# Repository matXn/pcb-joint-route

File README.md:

# PCB 多网络联合布线挑战

给定已经摆好元件的 PCB，让布线算法为多条网络一起决定走向、层和过孔。最想解决的问题是：**一条线准备占用狭窄通道时，算法能否预见其他网络要为它多绕多远，并在落线前改选方案？**

在 ESP32-S3-MINI-1 的一次实验中，GPIO46 从 3 个过孔减到了 1 个，和它争用空间的 GPIO38 却从 5.81 mm 绕到了 20.65 mm。只看 GPIO46 会把这次修改判为成功。这个题要求连同 GPIO38 和其余网络，一起衡量整组方案的代价。

## 要做什么

输入是板框、焊盘、网表、允许的层、设计规则和已经固定的铜。输出是一块可用 KiCad 打开和检查的 PCB，包含每条目标网络实际采用的线段和过孔。

我们尤其想看**由神经网络同时影响选线和布线**的方法。例如，用条件扩散模型为每条网络预测走线偏好，让各网交换对空间的需求。空旷区域可以保留多个可行方向，其他网络也需要穿过的瓶颈则应显示出更集中的偏好。模型还可以读取布线器试走后的冲突和绕行代价，修正先前的选择。热力图可用来解释选择，最终要用落到板上的铜线检验。也欢迎提交纯几何基线或其他可复现的方法。

## 数据

| 数据 | 内容 | 入口 |
|---|---|---|
| 训练集 | 60 块已布线的开源 KiCad 板，来自 48 个板族。其中 46 块双层、14 块四层。含原始 PCB、工程规则、结构化几何与参考走线 | [训练清单](data/train/manifest.json) |
| 训练候选 | 其中 45 块板附有 174 个候选路径文件，记录同一局部任务的多种走法、长度、过孔及候选间冲突 | [格式与来源](data/train/README.md) |
| 公开测试集 | 乐鑫 ESP32-S3-MINI-1 V1.1，一块模组，37 条 GPIO。提供可直接读取的 NumPy 网格、焊盘接入点和 KiCad 测试板重建工具 | [打开测试题](data/test/esp32s3-mini-1/README.md) |

本次新增 30 块板。按上游工程规则重新填铜后，这批板均为零 DRC 错误、零未连接，另外逐网核查了多焊盘网络的物理连通性。逐板错误和警告数量见[质量记录](data/train/quality.json)。

测试板单独留出。训练和选模型时，请按板族在训练集中划分验证数据。公开测试板的原始参考设计可以查到。用它来还原固定几何时，应先移除全部目标铜线，再提取用于布线、选线或调参的输入。反复根据这块板调整过的方法，请在报告中说明。

## 第一题 · ESP32-S3-MINI-1

模组尺寸为 15.4 × 20.5 mm，原板有四层。保留元件位置、晶振、电源、射频和其他固定线路，重新连接 37 条 GPIO 的全部 75 个焊盘。目标走线只能使用 F.Cu 和 B.Cu，允许水平、垂直和 45° 斜线，换层使用贯穿孔。GPIO45 有三个焊盘。天线禁布区、线宽、间距、孔径和层限制见[测试规格](data/test/esp32s3-mini-1/case.json)。

先检查每条 GPIO 的所有焊盘是否连通、固定线路是否保留、相对参考板是否引入新的 KiCad DRC 错误。通过后，再比较**目标过孔数、总铜线长度和转角数**。同时报告全板未连接项、运行时间和候选搜索预算。这样可以分辨一次改进来自模型决策、更多搜索，还是牺牲了另一项布线指标。

| 已测方案 | GPIO 接通 | 目标过孔 | 目标铜长 | 转角 | 新增 DRC 错误 |
|---|---:|---:|---:|---:|---:|
| 41 孔基线 | 37/37 | 41 | 197.34 mm | 140 | 0 |
| 联合选择，偏好少转角 | 37/37 | 39 | 212.99 mm | 126 | 0 |

参考板在 KiCad 10.0.6 导入后已有 57 项错误，两行均相对同一参考板逐项比较。39 孔方案从模型与布线器生成的完整单网候选中联合选择，省了 2 个孔和 14 个转角，多用了 15.65 mm 铜线。本题评估的是固定布局上的 GPIO 布线。

## 如何提交结果

可以在本仓库开一个 Issue，附上结果 PCB 或下载链接、算法说明、运行条件、KiCad DRC 报告和上表中的指标。如果使用神经网络，最好再提供一次**相同搜索预算下关闭模型引导**的结果。若展示热力图，欢迎选一处两条网争用的通道，画出两条网各自的偏好和最后采用的走法。

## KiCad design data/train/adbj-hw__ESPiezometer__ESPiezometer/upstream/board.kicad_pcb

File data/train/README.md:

# 训练数据

[manifest.json](manifest.json) 中的 60 块板按原项目家族归组，同一 `family` 的板应一起进入训练或验证。每条记录中的路径都相对于本目录。上游公开的是已完成布线的布局，具体由人工还是自动布线器完成未作标注。

| 文件 | 内容 |
|---|---|
| `<board_id>/upstream/` | 上游原始 KiCad 板、项目规则、许可证及署名说明，按下载字节保存 |
| `<board_id>/geometry.json` | 以毫米为单位的提取结果。`condition` 含板框、层、网表、焊盘和禁布区，`labels` 含实际线段、圆弧、过孔和覆铜轮廓。划定训练目标后，应从输入中去掉相应网络的标签 |
| `<board_id>/source.json` | 原项目、固定提交、原文件链接、SHA-256 和逐板许可 |
| `<board_id>/candidates/*.npz` | 部分板上的预计算布线候选。用 `numpy.load(path, allow_pickle=False)` 打开 |

候选文件内的 `meta` 是 JSON 字符串，给出板名、分支、网格及设计规则。`groups[i]` 标出第 i 个候选所属分支，`metric[i]` 依次为铜长（mm）、同层转角数、过孔数和顶层长度占比，`conflict[i,j]` 表示两候选存在跨网铜间距冲突。候选 i 的扁平节点序列为 `path_nodes[path_index[i]:path_index[i+1]]`，按 `meta.shape` 解码为层、行、列。首批选择器实验扫描了最初的 107 份候选文件，其中 20 块板的 73 份文件产生了有监督的双网比较样本。

## 可以从哪些板入手

| 双层板 | 学习场景 | 实际走线 |
|---|---|---|
| [Mitayi-Pico-D1](CIRCUITSTATE__Mitayi-Pico-D1__Mitayi-Pico-D1/upstream/board.kicad_pcb) | RP2040 核心板的引脚扇出 | 583 段直线、111 个过孔 |
| [Battery-Powered-STM32-Board-With-USB](mohamedboubaker__Battery-Powered-STM32-Board-With-USB__ORBIT/upstream/board.kicad_pcb) | STM32、USB 串口和电池充电电路 | 299 段直线、49 个过孔 |
| [RetroWiFiModem](mecparts__RetroWiFiModem__RetroWiFiModem/upstream/board.kicad_pcb) | 串口与 Wi-Fi 通信 | 318 段直线、63 个过孔 |
| [esphome-powermon](michd__esphome-powermon__esphome-powermon/upstream/board.kicad_pcb) | 多路电能监测与信号采集 | 225 段直线、15 个过孔 |

## 筛选与来源

本轮筛查了 122 块候选板。使用 KiCad 10.0.6 和原项目规则重新填铜，检查 DRC、未连接项和每条多焊盘网络的物理连通性。34 块通过这些检查并满足布线规模要求，再结合上游对完成度、已知问题和素材来源的说明，收录 30 块。新增板均为零 error、零未连接，其中 29 块仍有 warning。旧批次的 DRC 结果另行保留，两批均可按警告、错误和未连接数筛选。[逐板质量记录](quality.json)

按原件哈希和板框、焊盘位置、网络分组的几何签名去除重复。几何签名允许平移、旋转及镜像。还移除层数差异，与公开测试模组核对签名。请按 `family` 划分训练与验证，BrickPico 和 FanPico 共用一个板族。

样本通过 [pcb-corpus 固定目录](https://github.com/punkfab/pcb-corpus/tree/1e999b4eefd5fdfcc90dc376d2882390245a8e0d) 和硬件项目上游仓库发现。每块板的 `source.json` 指向具体提交、原作者和适用的硬件设计文件许可，`upstream/` 保存对应许可和署名。其中的第三方资料按其各自声明使用。针对每块板整理的几何和候选数据按该板许可提供。

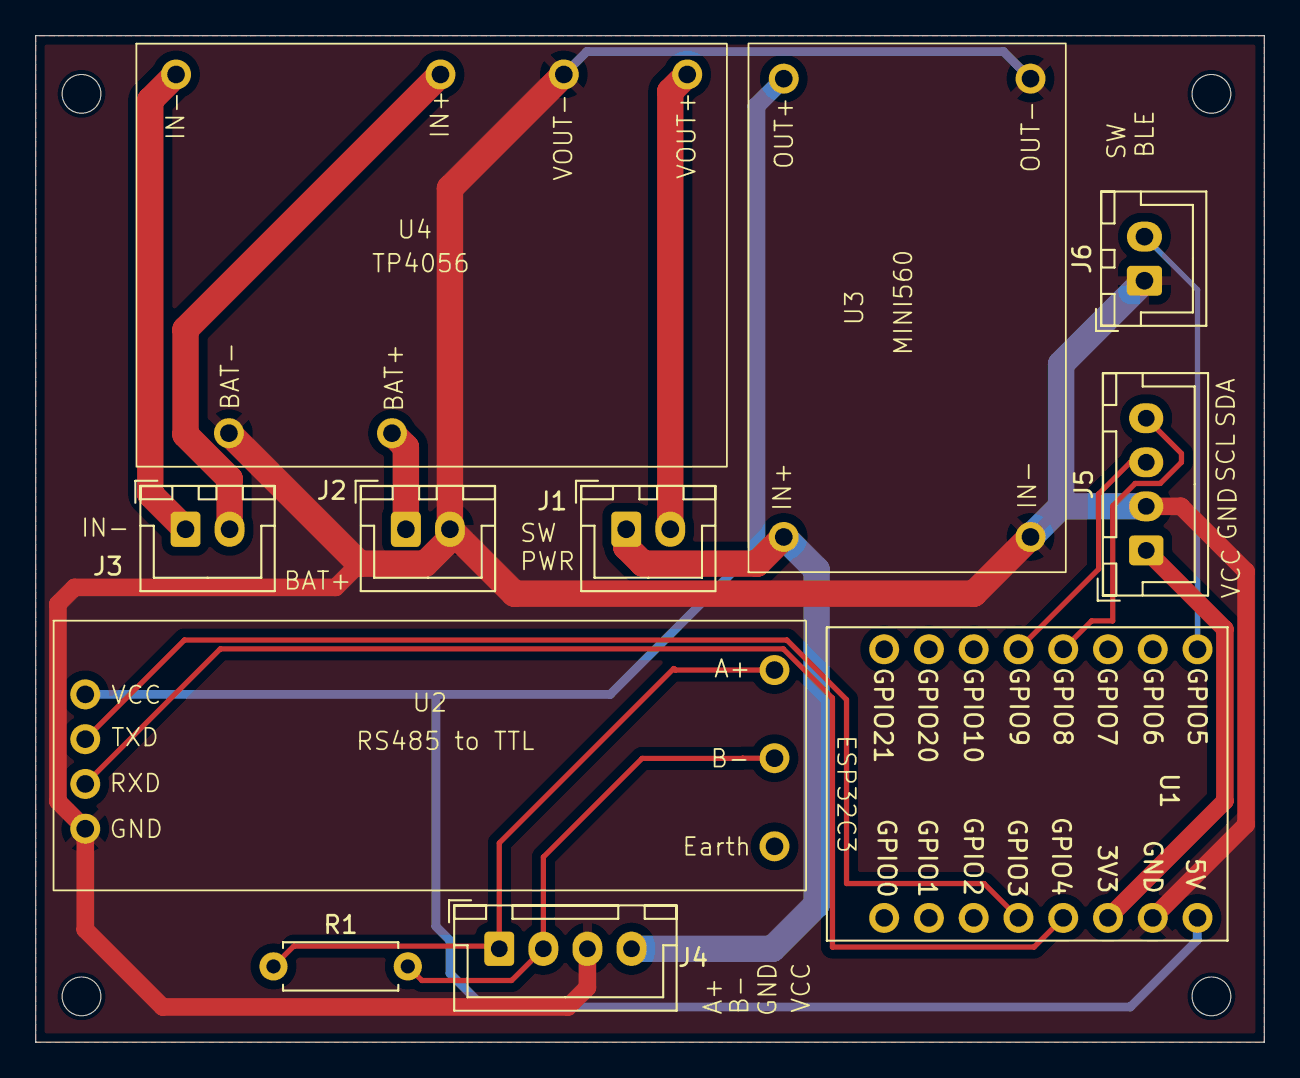
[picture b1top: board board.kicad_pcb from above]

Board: 2 copper layers, 69.7 x 57.1 mm, 11 parts (0 on the bottom side), 15 nets.

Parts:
J1, J2, J3, J6: Screw_Terminal_01x02; JST_XH_B2B-XH-A_1x02_P2.50mm_Vertical
J4, J5: Screw_Terminal_01x04; JST_XH_B4B-XH-A_1x04_P2.50mm_Vertical
R1: 120Ω; R_Axial_DIN0207_L6.3mm_D2.5mm_P7.62mm_Horizontal
U1: ESP32_C3_mni; ESP32_C3_MINI
U2: RS485_TTL_slim; RS485_TTL_Slim
U3: Mini560
U4: TP4056 battery charger; TP4056 baterry charger

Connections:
GND: J2.2, J4.3, J5.2, J6.1, U1.15 (GND), U2.1 (GND), U3.1 (IN-), U3.3 (OUT-), U4.3 (VOUT-), U4.5 (BAT-)
unnamed: J1.1, J4.4, U3.2 (IN+)
unnamed: J1.2, U4.4 (VOUT+)
unnamed: J2.1, U4.6 (BAT+)
unnamed: J3.1, U4.1 (IN-)
unnamed: J3.2, U4.2 (IN+)
unnamed: J4.1, R1.1, U2.7 (A+)
unnamed: J4.2, R1.2, U2.6 (B-)
unnamed: J5.1, U1.14 (3V3)
unnamed: J5.3, U1.4 (GPIO9)
unnamed: J5.4, U1.5 (GPIO8)
unnamed: J6.2, U1.8 (GPIO5)
unnamed: U1.16 (5V), U2.4 (VCC), U3.4 (OUT+)
unnamed: U1.12 (GPIO3), U2.3 (TXD)
unnamed: U1.13 (GPIO4), U2.2 (RXD)
